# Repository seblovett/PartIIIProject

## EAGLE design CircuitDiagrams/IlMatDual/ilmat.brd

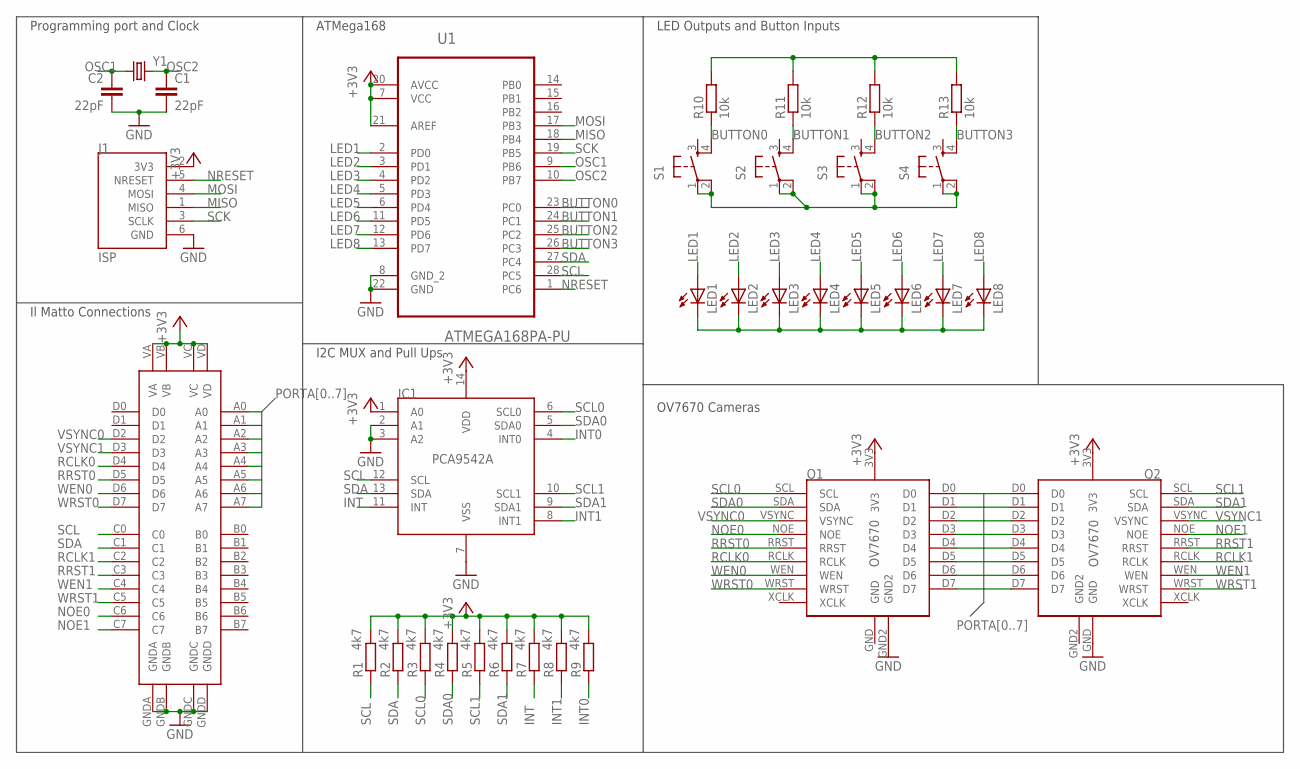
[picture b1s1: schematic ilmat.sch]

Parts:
C1, C2: 22pF; C025-024X044
IC1: PCA9542A; TSSOP14
J1: ISP; DUALHEAD_TH_6
LED1, LED2, LED3, LED4, LED5, LED6, LED7, LED8: LED-3MM-NO_SILK; LED3MM-NS
Q1, Q2: OV7670
R1, R2, R3, R4, R5, R6, R7, R8, R9: 4k7; V234/12
R10, R11, R12, R13: 10k; V234/12
S1, S2, S3, S4: TAC_SWITCHPTH; TACTILE-PTH
U1: ATMEGA168PA-PU; DIP254P762X457-28
U$1: ILMATTOSHEILD; ILMATSHEILD
Y1: CRYSTALHC49US; HC49US

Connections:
+3V3: IC1.1 (A0), IC1.14 (VDD), J1.2 (3V3), Q1.3V3, Q2.3V3, R1.2, R2.2, R3.2, R4.2, R5.2, R6.2, R7.2, R8.2, R9.2, U1.7 (VCC), U1.20 (AVCC), U1.21 (AREF), U$1.VA, U$1.VB, U$1.VC, U$1.VD
BUTTON0: R10.1, S1.4, U1.23 (PC0)
BUTTON1: R11.1, S2.4, U1.24 (PC1)
BUTTON2: R12.1, S3.4, U1.25 (PC2)
BUTTON3: R13.1, S4.4, U1.26 (PC3)
GND: C1.2, C2.2, IC1.2 (A1), IC1.3 (A2), IC1.7 (VSS), J1.6 (GND), Q1.GND, Q1.GND2, Q2.GND, U1.8 (GND_2), U1.22 (GND), U$1.GNDA, U$1.GNDB, U$1.GNDC, U$1.GNDD
GND2: Q2.GND2
INT: IC1.11 (INT), R7.1
INT0: IC1.4 (INT0), R9.1
INT1: IC1.8 (INT1), R8.1
LED1: LED1.A, U1.2 (PD0)
LED2: LED2.A, U1.3 (PD1)
LED3: LED3.A, U1.4 (PD2)
LED4: LED4.A, U1.5 (PD3)
LED5: LED5.A, U1.6 (PD4)
LED6: LED6.A, U1.11 (PD5)
LED7: LED7.A, U1.12 (PD6)
LED8: LED8.A, U1.13 (PD7)
MISO: J1.1 (MISO), U1.18 (PB4)
MOSI: J1.4 (MOSI), U1.17 (PB3)
unnamed: LED1.K (C), LED2.K (C), LED3.K (C), LED4.K (C), LED5.K (C), LED6.K (C), LED7.K (C), LED8.K (C)
unnamed: S1.1, S1.2, S2.1, S2.2, S3.1, S3.2, S4.1, S4.2
unnamed: R10.2, R11.2, R12.2, R13.2
NOE0: Q1.NOE, U$1.C6
NOE1: Q2.NOE, U$1.C7
NRESET: J1.5 (NRESET), U1.1 (PC6)
OSC1: C2.1, U1.9 (PB6), Y1.1
OSC2: C1.1, U1.10 (PB7), Y1.2
PORTA0: Q1.D0, Q2.D0, U$1.A0
PORTA1: Q1.D1, Q2.D1, U$1.A1
PORTA2: Q1.D2, Q2.D2, U$1.A2
PORTA3: Q1.D3, Q2.D3, U$1.A3
PORTA4: Q1.D4, Q2.D4, U$1.A4
PORTA5: Q1.D5, Q2.D5, U$1.A5
PORTA6: Q1.D6, Q2.D6, U$1.A6
PORTA7: Q1.D7, Q2.D7, U$1.A7
RCLK0: Q1.RCLK, U$1.D4
RCLK1: Q2.RCLK, U$1.C2
RRST0: Q1.RRST, U$1.D5
RRST1: Q2.RRST, U$1.C3
SCK: J1.3 (SCLK), U1.19 (PB5)
SCL: IC1.12 (SCL), R1.1, U1.28 (PC5), U$1.C0
SCL0: IC1.6 (SCL0), Q1.SCL, R3.1
SCL1: IC1.10 (SCL1), Q2.SCL, R5.1
SDA: IC1.13 (SDA), R2.1, U1.27 (PC4), U$1.C1
SDA0: IC1.5 (SDA0), Q1.SDA, R4.1
SDA1: IC1.9 (SDA1), Q2.SDA, R6.1
VSYNC0: Q1.VSYNC, U$1.D2
VSYNC1: Q2.VSYNC, U$1.D3
WEN0: Q1.WEN, U$1.D6
WEN1: Q2.WEN, U$1.C4
WRST0: Q1.WRST, U$1.D7
WRST1: Q2.WRST, U$1.C5

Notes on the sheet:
Programming port and Clock
ATMega168
Il Matto Connections
I2C MUX and Pull Ups
LED Outputs and Button Inputs
OV7670 Cameras

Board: 2 copper layers, 34 parts (0 on the bottom side), 52 nets, no tracks yet.

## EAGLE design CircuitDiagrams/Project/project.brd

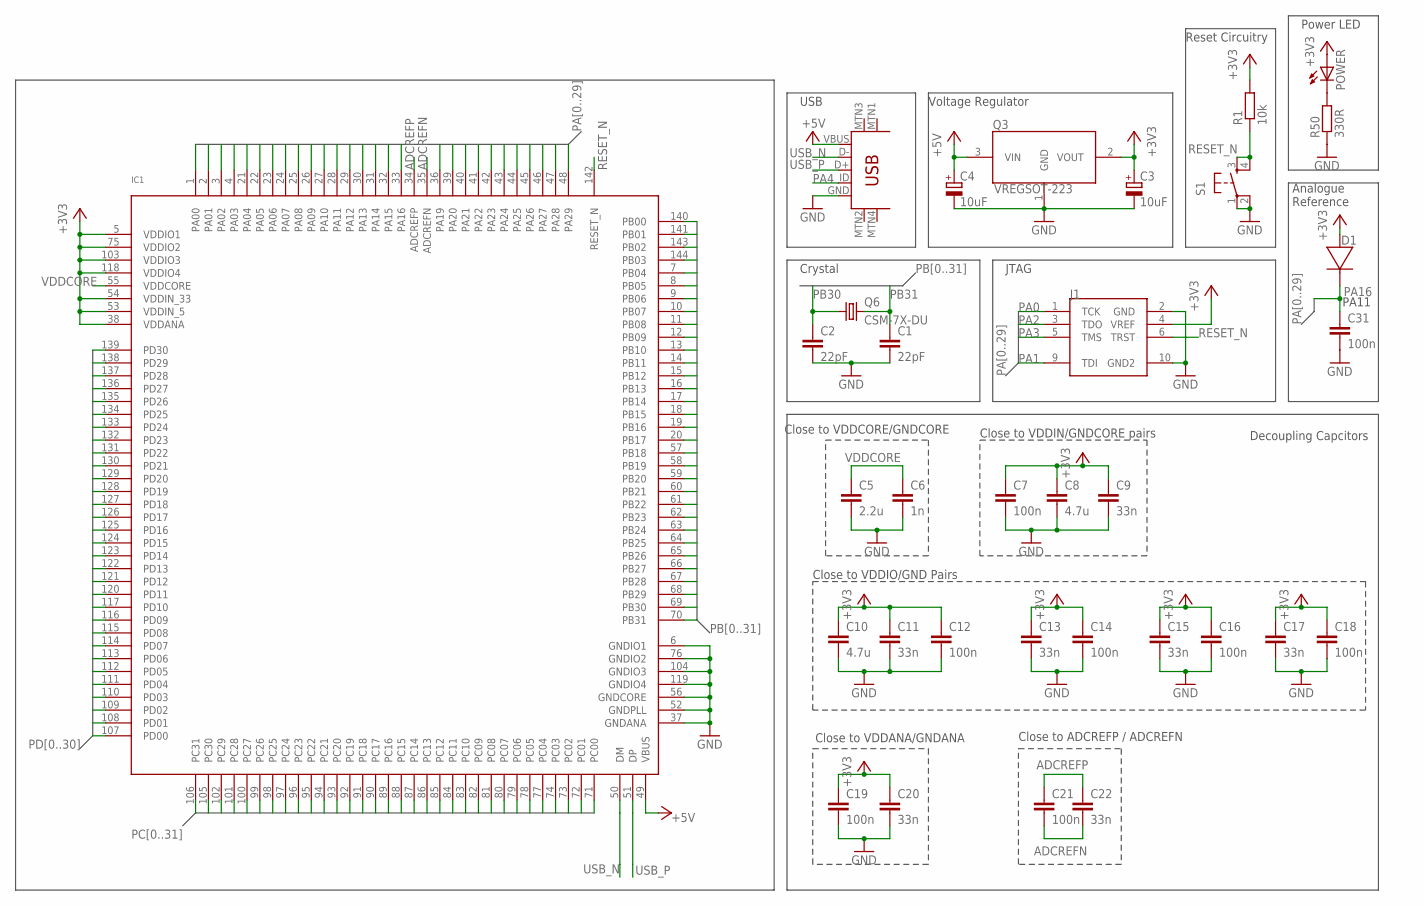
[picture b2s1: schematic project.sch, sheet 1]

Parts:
C1, C2: 22pF; C0603
C3, C4: 10uF; SMC_P
C5: 2.2u; C0603
C6: 1n; C0603
C7, C12, C14, C16, C18, C19, C21, C31: 100n; C0603
C8, C10: 4.7u; C0603
C9, C11, C13, C15, C17, C20, C22: 33n; C0603
D1: DIODESMD; SMC_C
IC1: UC3C; TQFP144
J1: JTAG2.54MM2X5TH; 2.54MM2X5TH
POWER: LED1206; LED-1206
Q3: VREGSOT-223; SOT-223
Q6: CSM-7X-DU
R1: 10k; R0603
R50: 330R; R0603
S1: TAC_SWITCHSMD; TACTILE_SWITCH_SMD
U$1: USB-MINIB-5PIN; USB-MINIB

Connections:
+3V3: C3.+, C7.1, C8.1, C9.1, C10.1, C11.1, C12.1, C13.1, C14.1, C15.1, C16.1, C17.1, C18.1, C19.1, C20.1, D1.+ (ANODE), IC1.5 (VDDIO1), IC1.38 (VDDANA), IC1.53 (VDDIN_5), IC1.54 (VDDIN_33), IC1.75 (VDDIO2), IC1.103 (VDDIO3), IC1.118 (VDDIO4), J1.4 (VREF), POWER.A, Q3.2 (VOUT), R1.2; also elsewhere on the board
+5V: C4.+, IC1.49 (VBUS), Q3.3 (VIN), U$1.VBUS; also elsewhere on the board
ADCREFN: C21.2, C22.2, IC1.35 (ADCREFN)
ADCREFP: C21.1, C22.1, IC1.34 (ADCREFP)
GND: C1.2, C2.2, C3.-, C4.-, C5.2, C6.2, C7.2, C8.2, C9.2, C10.2, C11.2, C12.2, C13.2, C14.2, C15.2, C16.2, C17.2, C18.2, C19.2, C20.2, C31.2, IC1.6 (GNDIO1), IC1.37 (GNDANA), IC1.52 (GNDPLL), IC1.56 (GNDCORE), IC1.76 (GNDIO2), IC1.104 (GNDIO3), IC1.119 (GNDIO4), J1.2 (GND), J1.10 (GND2), Q3.1 (GND), R50.1, S1.1, S1.2, U$1.GND; also elsewhere on the board
unnamed: POWER.C, R50.2
PA0: IC1.1 (PA00), J1.1 (TCK)
PA1: IC1.2 (PA01), J1.9 (TDI)
PA2: IC1.3 (PA02), J1.3 (TDO)
PA3: IC1.4 (PA03), J1.5 (TMS)
PA4: IC1.21 (PA04), U$1.ID
PA5: IC1.22 (PA05); also elsewhere on the board
PA6: IC1.23 (PA06); also elsewhere on the board
PA7: IC1.24 (PA07); also elsewhere on the board
PA8: IC1.25 (PA08); also elsewhere on the board
PA9: IC1.26 (PA09); also elsewhere on the board
PA10: IC1.27 (PA10); also elsewhere on the board
PA12: IC1.29 (PA12); also elsewhere on the board
PA13: IC1.30 (PA13); also elsewhere on the board
PA14: IC1.31 (PA14); also elsewhere on the board
PA15: IC1.32 (PA15); also elsewhere on the board
PA16: C31.1, D1.- (CATHODE), IC1.28 (PA11), IC1.33 (PA16)
PA19: IC1.36 (PA19); also elsewhere on the board
PA20: IC1.39 (PA20); also elsewhere on the board
PA21: IC1.40 (PA21); also elsewhere on the board
PA22: IC1.41 (PA22); also elsewhere on the board
PA23: IC1.42 (PA23); also elsewhere on the board
PA24: IC1.43 (PA24); also elsewhere on the board
PA25: IC1.44 (PA25); also elsewhere on the board
PA26: IC1.45 (PA26); also elsewhere on the board
PA27: IC1.46 (PA27); also elsewhere on the board
PA28: IC1.47 (PA28); also elsewhere on the board
PA29: IC1.48 (PA29); also elsewhere on the board
PB0: IC1.140 (PB00); also elsewhere on the board
PB1: IC1.141 (PB01); also elsewhere on the board
PB2: IC1.143 (PB02); also elsewhere on the board
PB3: IC1.144 (PB03); also elsewhere on the board
PB4: IC1.7 (PB04); also elsewhere on the board
PB5: IC1.8 (PB05); also elsewhere on the board
PB6: IC1.9 (PB06); also elsewhere on the board
PB7: IC1.10 (PB07); also elsewhere on the board
PB8: IC1.11 (PB08); also elsewhere on the board
PB9: IC1.12 (PB09); also elsewhere on the board
PB10: IC1.13 (PB10); also elsewhere on the board
PB11: IC1.14 (PB11); also elsewhere on the board
PB12: IC1.15 (PB12); also elsewhere on the board
PB13: IC1.16 (PB13); also elsewhere on the board
PB14: IC1.17 (PB14); also elsewhere on the board
PB15: IC1.18 (PB15); also elsewhere on the board
PB16: IC1.19 (PB16); also elsewhere on the board
PB17: IC1.20 (PB17); also elsewhere on the board
PB18: IC1.57 (PB18); also elsewhere on the board
PB19: IC1.58 (PB19); also elsewhere on the board
PB20: IC1.59 (PB20); also elsewhere on the board
PB21: IC1.60 (PB21); also elsewhere on the board
PB22: IC1.61 (PB22); also elsewhere on the board
PB23: IC1.62 (PB23); also elsewhere on the board
PB24: IC1.63 (PB24); also elsewhere on the board
PB25: IC1.64 (PB25); also elsewhere on the board
PB26: IC1.65 (PB26); also elsewhere on the board
PB27: IC1.66 (PB27); also elsewhere on the board
PB28: IC1.67 (PB28); also elsewhere on the board
PB29: IC1.68 (PB29); also elsewhere on the board
PB30: C2.1, IC1.69 (PB30), Q6.1
PB31: C1.1, IC1.70 (PB31), Q6.2
PC0: IC1.71 (PC00); also elsewhere on the board
PC1: IC1.72 (PC01); also elsewhere on the board
PC2: IC1.73 (PC02); also elsewhere on the board
PC3: IC1.74 (PC03); also elsewhere on the board
PC4: IC1.77 (PC04); also elsewhere on the board
PC5: IC1.78 (PC05); also elsewhere on the board
PC6: IC1.79 (PC06); also elsewhere on the board
PC7: IC1.80 (PC07)
PC8: IC1.81 (PC08); also elsewhere on the board
PC9: IC1.82 (PC09); also elsewhere on the board
PC10: IC1.83 (PC10); also elsewhere on the board
PC11: IC1.84 (PC11); also elsewhere on the board
PC12: IC1.85 (PC12); also elsewhere on the board
PC13: IC1.86 (PC13); also elsewhere on the board
PC14: IC1.87 (PC14); also elsewhere on the board
PC15: IC1.88 (PC15); also elsewhere on the board
PC16: IC1.89 (PC16); also elsewhere on the board
PC17: IC1.90 (PC17); also elsewhere on the board
PC18: IC1.91 (PC18); also elsewhere on the board
PC19: IC1.92 (PC19); also elsewhere on the board
PC20: IC1.93 (PC20); also elsewhere on the board
PC21: IC1.94 (PC21); also elsewhere on the board
PC22: IC1.95 (PC22); also elsewhere on the board
PC23: IC1.96 (PC23); also elsewhere on the board
PC24: IC1.97 (PC24); also elsewhere on the board
PC25: IC1.98 (PC25); also elsewhere on the board
PC26: IC1.99 (PC26); also elsewhere on the board
PC27: IC1.100 (PC27); also elsewhere on the board
PC28: IC1.101 (PC28); also elsewhere on the board
PC29: IC1.102 (PC29); also elsewhere on the board
PC30: IC1.105 (PC30); also elsewhere on the board
PC31: IC1.106 (PC31); also elsewhere on the board
PD0: IC1.107 (PD00); also elsewhere on the board
PD1: IC1.108 (PD01); also elsewhere on the board
PD2: IC1.109 (PD02); also elsewhere on the board
PD3: IC1.110 (PD03); also elsewhere on the board
PD4: IC1.111 (PD04); also elsewhere on the board
PD5: IC1.112 (PD05); also elsewhere on the board
PD6: IC1.113 (PD06); also elsewhere on the board
PD7: IC1.114 (PD07); also elsewhere on the board
PD8: IC1.115 (PD08); also elsewhere on the board
PD9: IC1.116 (PD09); also elsewhere on the board
PD10: IC1.117 (PD10); also elsewhere on the board
PD11: IC1.120 (PD11); also elsewhere on the board
PD12: IC1.121 (PD12); also elsewhere on the board
PD13: IC1.122 (PD13); also elsewhere on the board
PD14: IC1.123 (PD14); also elsewhere on the board
PD15: IC1.124 (PD15); also elsewhere on the board
PD16: IC1.125 (PD16)
PD17: IC1.126 (PD17); also elsewhere on the board
PD18: IC1.127 (PD18)
PD19: IC1.128 (PD19)
PD20: IC1.129 (PD20); also elsewhere on the board
PD21: IC1.130 (PD21); also elsewhere on the board
PD22: IC1.131 (PD22)
PD23: IC1.132 (PD23); also elsewhere on the board
PD24: IC1.133 (PD24); also elsewhere on the board
PD25: IC1.134 (PD25); also elsewhere on the board
PD26: IC1.135 (PD26); also elsewhere on the board
PD27: IC1.136 (PD27); also elsewhere on the board
PD28: IC1.137 (PD28); also elsewhere on the board
PD29: IC1.138 (PD29); also elsewhere on the board
PD30: IC1.139 (PD30); also elsewhere on the board
RESET_N: IC1.142 (RESET_N), J1.6 (TRST), R1.1, S1.3, S1.4
USB_N: IC1.50 (DM), U$1.D-
USB_P: IC1.51 (DP), U$1.D+
VDDCORE: C5.1, C6.1, IC1.55 (VDDCORE)

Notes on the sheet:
JTAG
USB
Reset Circuitry
Voltage Regulator
Crystal
Decoupling Capcitors
Close to VDDCORE/GNDCORE
Close to VDDIN/GNDCORE pairs
Close to VDDIO/GND Pairs
Close to VDDANA/GNDANA
Close to ADCREFP / ADCREFN
PA11
Analogue Reference
Power LED

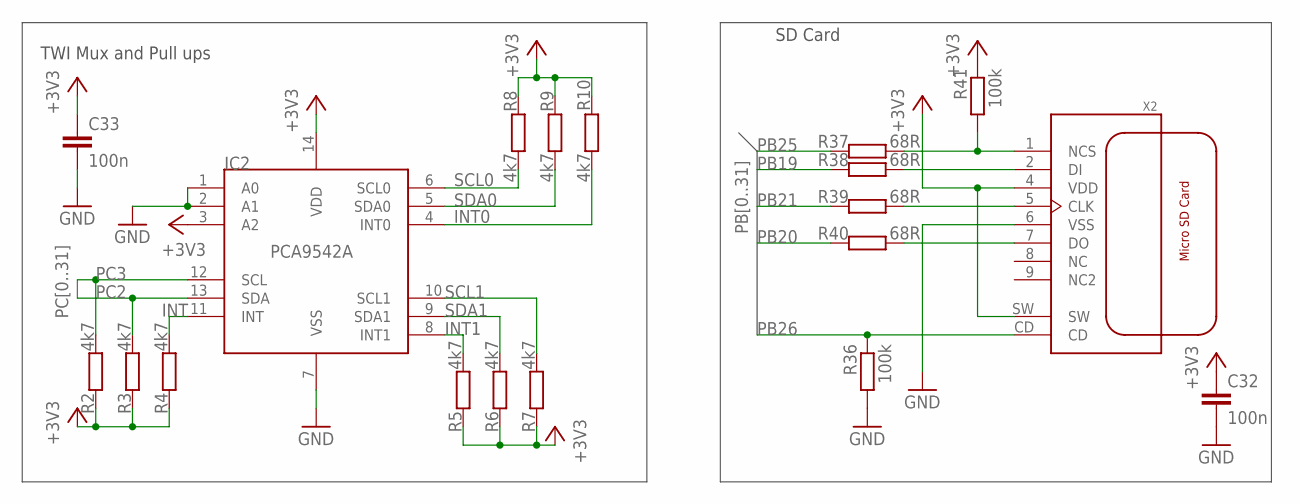
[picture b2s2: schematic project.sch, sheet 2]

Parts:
C32, C33: 100n; C0603
IC2: PCA9542A; TSSOP14
R2, R3, R4, R5, R6, R7, R8, R9, R10: 4k7; R0603
R36, R41: 100k; R0603
R37, R38, R39, R40: 68R; R0603
X2: MICROSDSMD; MICROSD

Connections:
+3V3: C32.1, C33.1, IC2.3 (A2), IC2.14 (VDD), R2.1, R3.1, R4.1, R5.1, R6.1, R7.1, R8.1, R9.1, R10.1, R41.1, X2.4 (VDD), X2.SW; also elsewhere on the board
GND: C32.2, C33.2, IC2.1 (A0), IC2.2 (A1), IC2.7 (VSS), R36.2, X2.6 (VSS); also elsewhere on the board
INT: IC2.11 (INT), R4.2
INT0: IC2.4 (INT0), R10.2
INT1: IC2.8 (INT1), R5.2
unnamed: R37.2, R41.2, X2.1 (NCS)
unnamed: R38.2, X2.2 (DI)
unnamed: R39.2, X2.5 (CLK)
unnamed: R40.2, X2.7 (DO)
PB19: R38.1; also elsewhere on the board
PB20: R40.1; also elsewhere on the board
PB21: R39.1; also elsewhere on the board
PB25: R37.1; also elsewhere on the board
PB26: R36.1, X2.CD; also elsewhere on the board
PC2: IC2.13 (SDA), R3.2; also elsewhere on the board
PC3: IC2.12 (SCL), R2.2; also elsewhere on the board
SCL0: IC2.6 (SCL0), R8.2; also elsewhere on the board
SCL1: IC2.10 (SCL1), R7.2; also elsewhere on the board
SDA0: IC2.5 (SDA0), R9.2; also elsewhere on the board
SDA1: IC2.9 (SDA1), R6.2; also elsewhere on the board

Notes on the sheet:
TWI Mux and Pull ups
SD Card

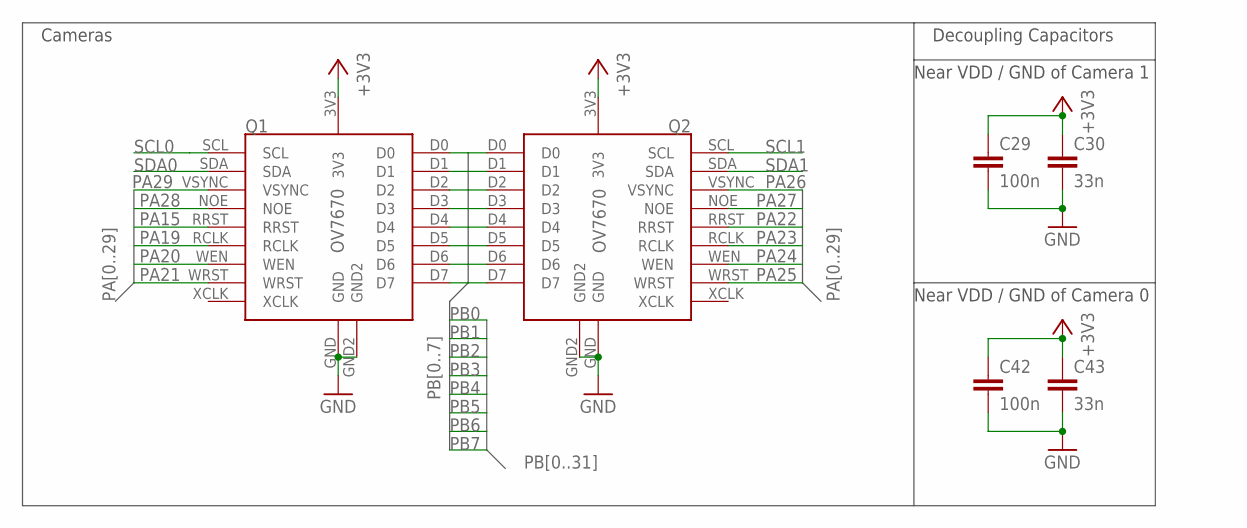
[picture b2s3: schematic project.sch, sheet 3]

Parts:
C29, C42: 100n; C0603
C30, C43: 33n; C0603
Q1, Q2: OV7670

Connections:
+3V3: C29.1, C30.1, C42.1, C43.1, Q1.3V3, Q2.3V3; also elsewhere on the board
GND: C29.2, C30.2, C42.2, C43.2, Q1.GND, Q1.GND2, Q2.GND, Q2.GND2; also elsewhere on the board
PA15: Q1.RRST; also elsewhere on the board
PA19: Q1.RCLK; also elsewhere on the board
PA20: Q1.WEN; also elsewhere on the board
PA21: Q1.WRST; also elsewhere on the board
PA22: Q2.RRST; also elsewhere on the board
PA23: Q2.RCLK; also elsewhere on the board
PA24: Q2.WEN; also elsewhere on the board
PA25: Q2.WRST; also elsewhere on the board
PA26: Q2.VSYNC; also elsewhere on the board
PA27: Q2.NOE; also elsewhere on the board
PA28: Q1.NOE; also elsewhere on the board
PA29: Q1.VSYNC; also elsewhere on the board
PB0: Q1.D0, Q2.D0; also elsewhere on the board
PB1: Q1.D1, Q2.D1; also elsewhere on the board
PB2: Q1.D2, Q2.D2; also elsewhere on the board
PB3: Q1.D3, Q2.D3; also elsewhere on the board
PB4: Q1.D4, Q2.D4; also elsewhere on the board
PB5: Q1.D5, Q2.D5; also elsewhere on the board
PB6: Q1.D6, Q2.D6; also elsewhere on the board
PB7: Q1.D7, Q2.D7; also elsewhere on the board
SCL0: Q1.SCL; also elsewhere on the board
SCL1: Q2.SCL; also elsewhere on the board
SDA0: Q1.SDA; also elsewhere on the board
SDA1: Q2.SDA; also elsewhere on the board

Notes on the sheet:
Cameras
Decoupling Capacitors
Near VDD / GND of Camera 0
Near VDD / GND of Camera 1

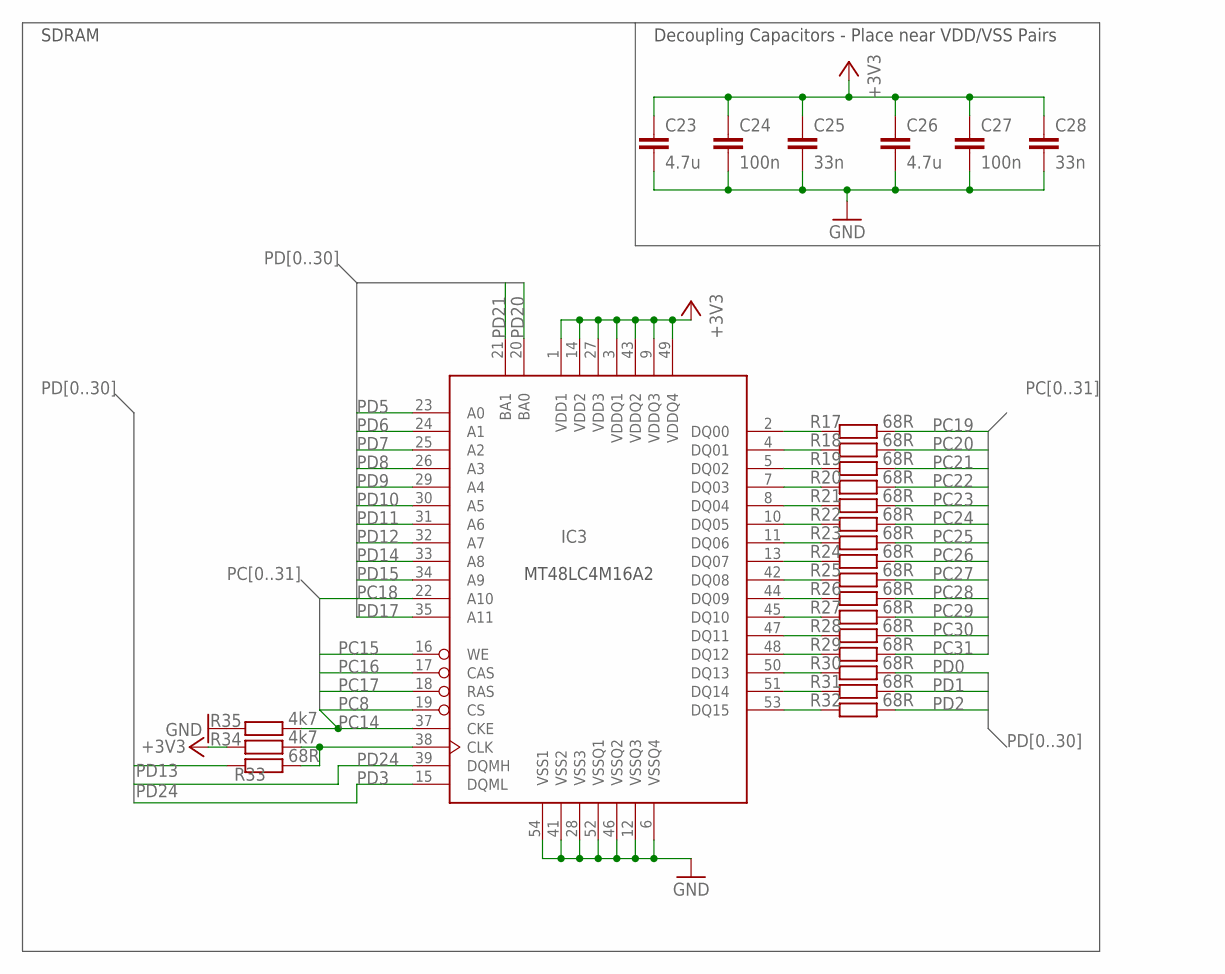
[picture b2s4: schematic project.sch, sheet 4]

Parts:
C23, C26: 4.7u; C0603
C24, C27: 100n; C0603
C25, C28: 33n; C0603
IC3: MT48LC4M16A2TSOP54; TSOP54
R17, R18, R19, R20, R21, R22, R23, R24, R25, R26, R27, R28, R29, R30, R31, R32, R33: 68R; R0603
R34, R35: 4k7; R0603

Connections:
+3V3: C23.1, C24.1, C25.1, C26.1, C27.1, C28.1, IC3.1 (VDD1), IC3.3 (VDDQ1), IC3.9 (VDDQ3), IC3.14 (VDD2), IC3.27 (VDD3), IC3.43 (VDDQ2), IC3.49 (VDDQ4), R34.1; also elsewhere on the board
DQ00: IC3.2 (DQ00), R17.1
DQ01: IC3.4 (DQ01), R18.1
DQ02: IC3.5 (DQ02), R19.1
DQ03: IC3.7 (DQ03), R20.1
DQ04: IC3.8 (DQ04), R21.1
DQ05: IC3.10 (DQ05), R22.1
DQ06: IC3.11 (DQ06), R23.1
DQ07: IC3.13 (DQ07), R24.1
DQ08: IC3.42 (DQ08), R25.1
DQ09: IC3.44 (DQ09), R26.1
DQ10: IC3.45 (DQ10), R27.1
DQ11: IC3.47 (DQ11), R28.1
DQ12: IC3.48 (DQ12), R29.1
DQ13: IC3.50 (DQ13), R30.1
DQ14: IC3.51 (DQ14), R31.1
DQ15: IC3.53 (DQ15), R32.1
GND: C23.2, C24.2, C25.2, C26.2, C27.2, C28.2, IC3.6 (VSSQ4), IC3.12 (VSSQ3), IC3.28 (VSS3), IC3.41 (VSS2), IC3.46 (VSSQ2), IC3.52 (VSSQ1), IC3.54 (VSS1), R35.1; also elsewhere on the board
PC8: IC3.19 (CS); also elsewhere on the board
PC14: IC3.37 (CKE), R35.2; also elsewhere on the board
PC15: IC3.16 (WE); also elsewhere on the board
PC16: IC3.17 (CAS); also elsewhere on the board
PC17: IC3.18 (RAS); also elsewhere on the board
PC18: IC3.22 (A10); also elsewhere on the board
PC19: R17.2; also elsewhere on the board
PC20: R18.2; also elsewhere on the board
PC21: R19.2; also elsewhere on the board
PC22: R20.2; also elsewhere on the board
PC23: R21.2; also elsewhere on the board
PC24: R22.2; also elsewhere on the board
PC25: R23.2; also elsewhere on the board
PC26: R24.2; also elsewhere on the board
PC27: R25.2; also elsewhere on the board
PC28: R26.2; also elsewhere on the board
PC29: R27.2; also elsewhere on the board
PC30: R28.2; also elsewhere on the board
PC31: R29.2; also elsewhere on the board
PD0: R30.2; also elsewhere on the board
PD1: R31.2; also elsewhere on the board
PD2: R32.2; also elsewhere on the board
PD3: IC3.15 (DQML); also elsewhere on the board
PD5: IC3.23 (A0); also elsewhere on the board
PD6: IC3.24 (A1); also elsewhere on the board
PD7: IC3.25 (A2); also elsewhere on the board
PD8: IC3.26 (A3); also elsewhere on the board
PD9: IC3.29 (A4); also elsewhere on the board
PD10: IC3.30 (A5); also elsewhere on the board
PD11: IC3.31 (A6); also elsewhere on the board
PD12: IC3.32 (A7); also elsewhere on the board
PD13: R33.1; also elsewhere on the board
PD14: IC3.33 (A8); also elsewhere on the board
PD15: IC3.34 (A9); also elsewhere on the board
PD17: IC3.35 (A11); also elsewhere on the board
PD20: IC3.20 (BA0); also elsewhere on the board
PD21: IC3.21 (BA1); also elsewhere on the board
PD24: IC3.39 (DQMH); also elsewhere on the board
SDRAMCLK: IC3.38 (CLK), R33.2, R34.2

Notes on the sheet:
SDRAM
Decoupling Capacitors - Place near VDD/VSS Pairs

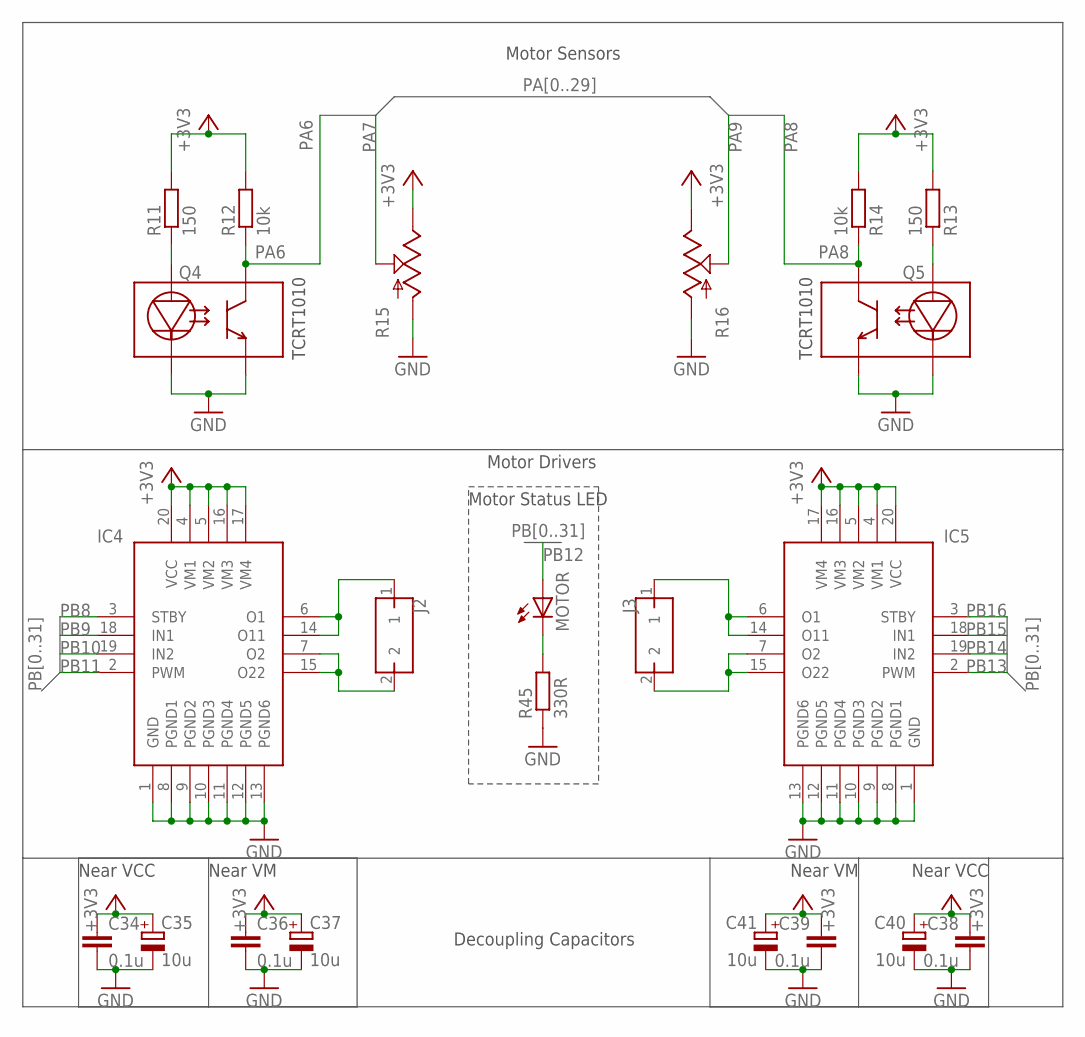
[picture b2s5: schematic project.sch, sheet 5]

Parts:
C34, C36, C38, C39: 0.1u; C0603
C35, C37, C40, C41: 10u; SMC_Z
IC4, IC5: TB6593FNGSSOP20; SSOP20
J2, J3: 1BY2THROUGHHOLE; 1BY2
MOTOR: LED1206; LED-1206
Q4, Q5: TCRT1010TH; TCRT1010
R11, R13: 150; R0603
R12, R14: 10k; R0603
R15, R16: POTTRIM; TRIM_POT
R45: 330R; R0603

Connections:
+3V3: C34.1, C35.+, C36.1, C37.+, C38.1, C39.1, C40.+, C41.+, IC4.4 (VM1), IC4.5 (VM2), IC4.16 (VM3), IC4.17 (VM4), IC4.20 (VCC), IC5.4 (VM1), IC5.5 (VM2), IC5.16 (VM3), IC5.17 (VM4), IC5.20 (VCC), R11.2, R12.2, R13.2, R14.2, R15.2 (E), R16.2 (E); also elsewhere on the board
GND: C34.2, C35.-, C36.2, C37.-, C38.2, C39.2, C40.-, C41.-, IC4.1 (GND), IC4.8 (PGND1), IC4.9 (PGND2), IC4.10 (PGND3), IC4.11 (PGND4), IC4.12 (PGND5), IC4.13 (PGND6), IC5.1 (GND), IC5.8 (PGND1), IC5.9 (PGND2), IC5.10 (PGND3), IC5.11 (PGND4), IC5.12 (PGND5), IC5.13 (PGND6), Q4.CATHODE, Q4.EMMITTER, Q5.CATHODE, Q5.EMMITTER, R15.3 (A), R16.3 (A), R45.1; also elsewhere on the board
M11: IC4.6 (O1), IC4.14 (O11), J2.1
M12: IC4.7 (O2), IC4.15 (O22), J2.2
M21: IC5.6 (O1), IC5.14 (O11), J3.1
M22: IC5.7 (O2), IC5.15 (O22), J3.2
unnamed: Q4.ANODE, R11.1
unnamed: Q5.ANODE, R13.1
unnamed: MOTOR.C, R45.2
PA6: Q4.COLLECTOR, R12.1; also elsewhere on the board
PA7: R15.1 (S); also elsewhere on the board
PA8: Q5.COLLECTOR, R14.1; also elsewhere on the board
PA9: R16.1 (S); also elsewhere on the board
PB8: IC4.3 (STBY); also elsewhere on the board
PB9: IC4.18 (IN1); also elsewhere on the board
PB10: IC4.19 (IN2); also elsewhere on the board
PB11: IC4.2 (PWM); also elsewhere on the board
PB12: MOTOR.A; also elsewhere on the board
PB13: IC5.2 (PWM); also elsewhere on the board
PB14: IC5.19 (IN2); also elsewhere on the board
PB15: IC5.18 (IN1); also elsewhere on the board
PB16: IC5.3 (STBY); also elsewhere on the board

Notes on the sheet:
Motor Drivers
Motor Sensors
Decoupling Capacitors
Near VCC
Near VM
Motor Status LED

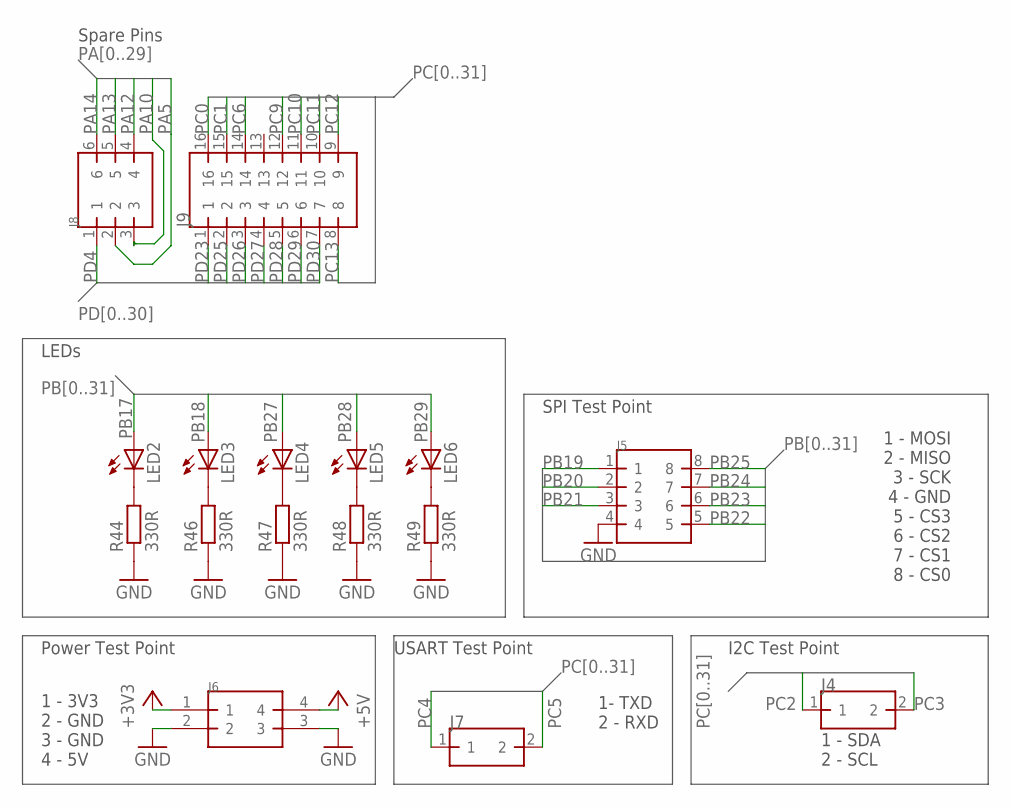
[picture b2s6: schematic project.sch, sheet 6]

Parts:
J4, J7: 1BY2THROUGHHOLE; 1BY2
J5: 8PIN2.54MM2X4TH; 2.54MM2X4TH
J6: 4PIN2.54MM2X2TH; 2.54MM2X2TH
J8: 6PIN2.54MM2X3TH; 2.54MM2X3TH
J9: 16PIN2.54MM2X8TH; 2.54MM2X8TH
LED2, LED3, LED4, LED5, LED6: LED1206; LED-1206
R44, R46, R47, R48, R49: 330R; R0603

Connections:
+3V3: J6.1; also elsewhere on the board
+5V: J6.4; also elsewhere on the board
GND: J5.4, J6.2, J6.3, R44.1, R46.1, R47.1, R48.1, R49.1; also elsewhere on the board
unnamed: LED2.C, R44.2
unnamed: LED3.C, R46.2
unnamed: LED4.C, R47.2
unnamed: LED5.C, R48.2
unnamed: LED6.C, R49.2
PA5: J8.2; also elsewhere on the board
PA10: J8.3; also elsewhere on the board
PA12: J8.4; also elsewhere on the board
PA13: J8.5; also elsewhere on the board
PA14: J8.6; also elsewhere on the board
PB17: LED2.A; also elsewhere on the board
PB18: LED3.A; also elsewhere on the board
PB19: J5.1; also elsewhere on the board
PB20: J5.2; also elsewhere on the board
PB21: J5.3; also elsewhere on the board
PB22: J5.5; also elsewhere on the board
PB23: J5.6; also elsewhere on the board
PB24: J5.7; also elsewhere on the board
PB25: J5.8; also elsewhere on the board
PB27: LED4.A; also elsewhere on the board
PB28: LED5.A; also elsewhere on the board
PB29: LED6.A; also elsewhere on the board
PC0: J9.16; also elsewhere on the board
PC1: J9.15; also elsewhere on the board
PC2: J4.1; also elsewhere on the board
PC3: J4.2; also elsewhere on the board
PC4: J7.1; also elsewhere on the board
PC5: J7.2; also elsewhere on the board
PC6: J9.14; also elsewhere on the board
PC9: J9.12; also elsewhere on the board
PC10: J9.11; also elsewhere on the board
PC11: J9.10; also elsewhere on the board
PC12: J9.9; also elsewhere on the board
PC13: J9.8; also elsewhere on the board
PD4: J8.1; also elsewhere on the board
PD23: J9.1; also elsewhere on the board
PD25: J9.2; also elsewhere on the board
PD26: J9.3; also elsewhere on the board
PD27: J9.4; also elsewhere on the board
PD28: J9.5; also elsewhere on the board
PD29: J9.6; also elsewhere on the board
PD30: J9.7; also elsewhere on the board

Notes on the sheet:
I2C Test Point
1 - MOSI 2 - MISO 3 - SCK 4 - GND 5 - CS3 6 - CS2 7 - CS1 8 - CS0
1 - SDA 2 - SCL
SPI Test Point
Power Test Point
1 - 3V3 2 - GND 3 - GND 4 - 5V
USART Test Point
1- TXD 2 - RXD
LEDs
Spare Pins

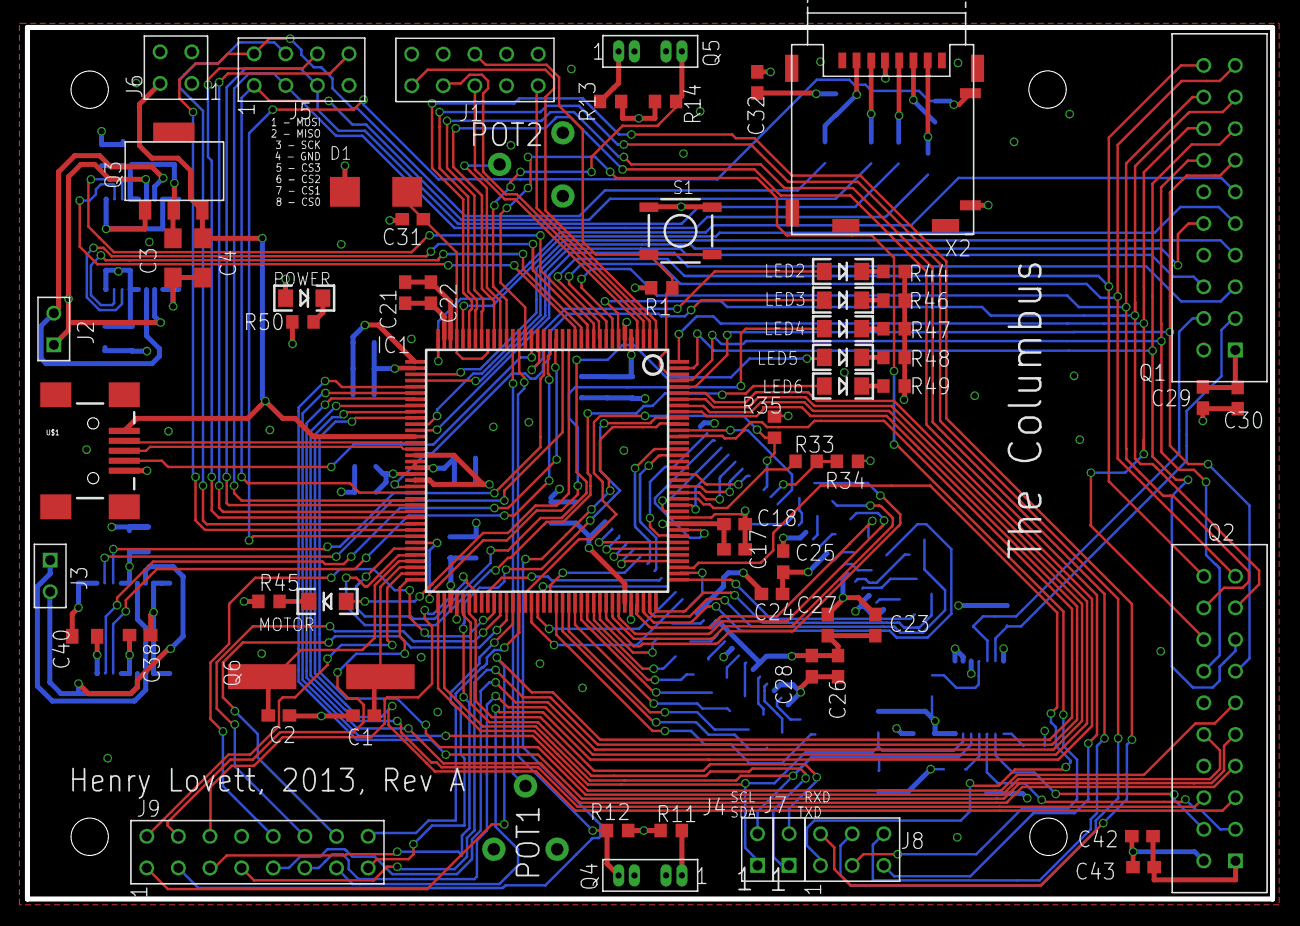
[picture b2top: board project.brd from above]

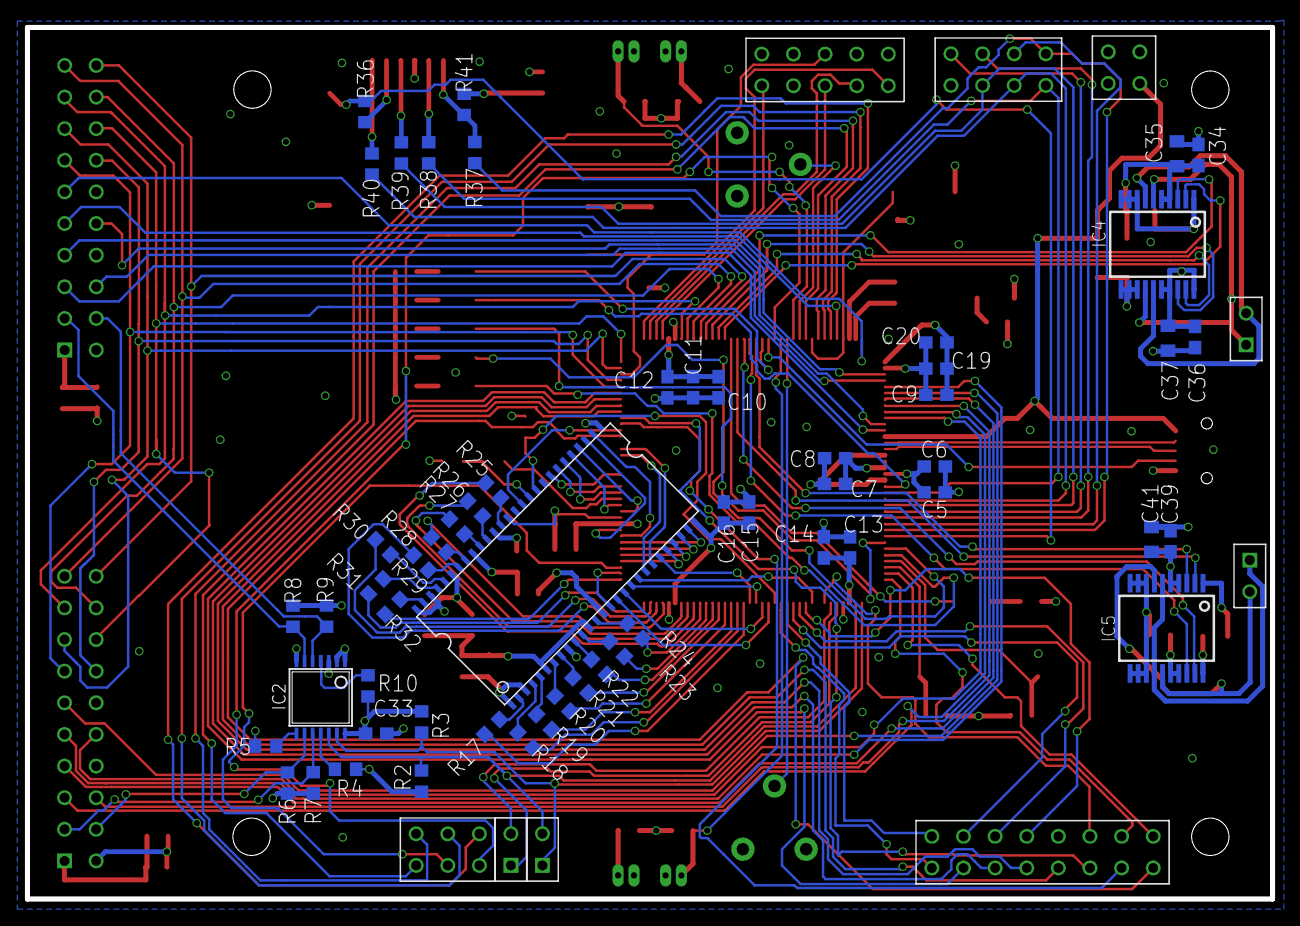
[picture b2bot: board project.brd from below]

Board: 4 copper layers, 100.0 x 70.0 mm, 122 parts (56 on the bottom side), 167 nets.

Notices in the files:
parts and their libraries:
SparkFun: Licensing: CC v3.0 Share-Alike You are welcome to use this library for commercial purposes.
